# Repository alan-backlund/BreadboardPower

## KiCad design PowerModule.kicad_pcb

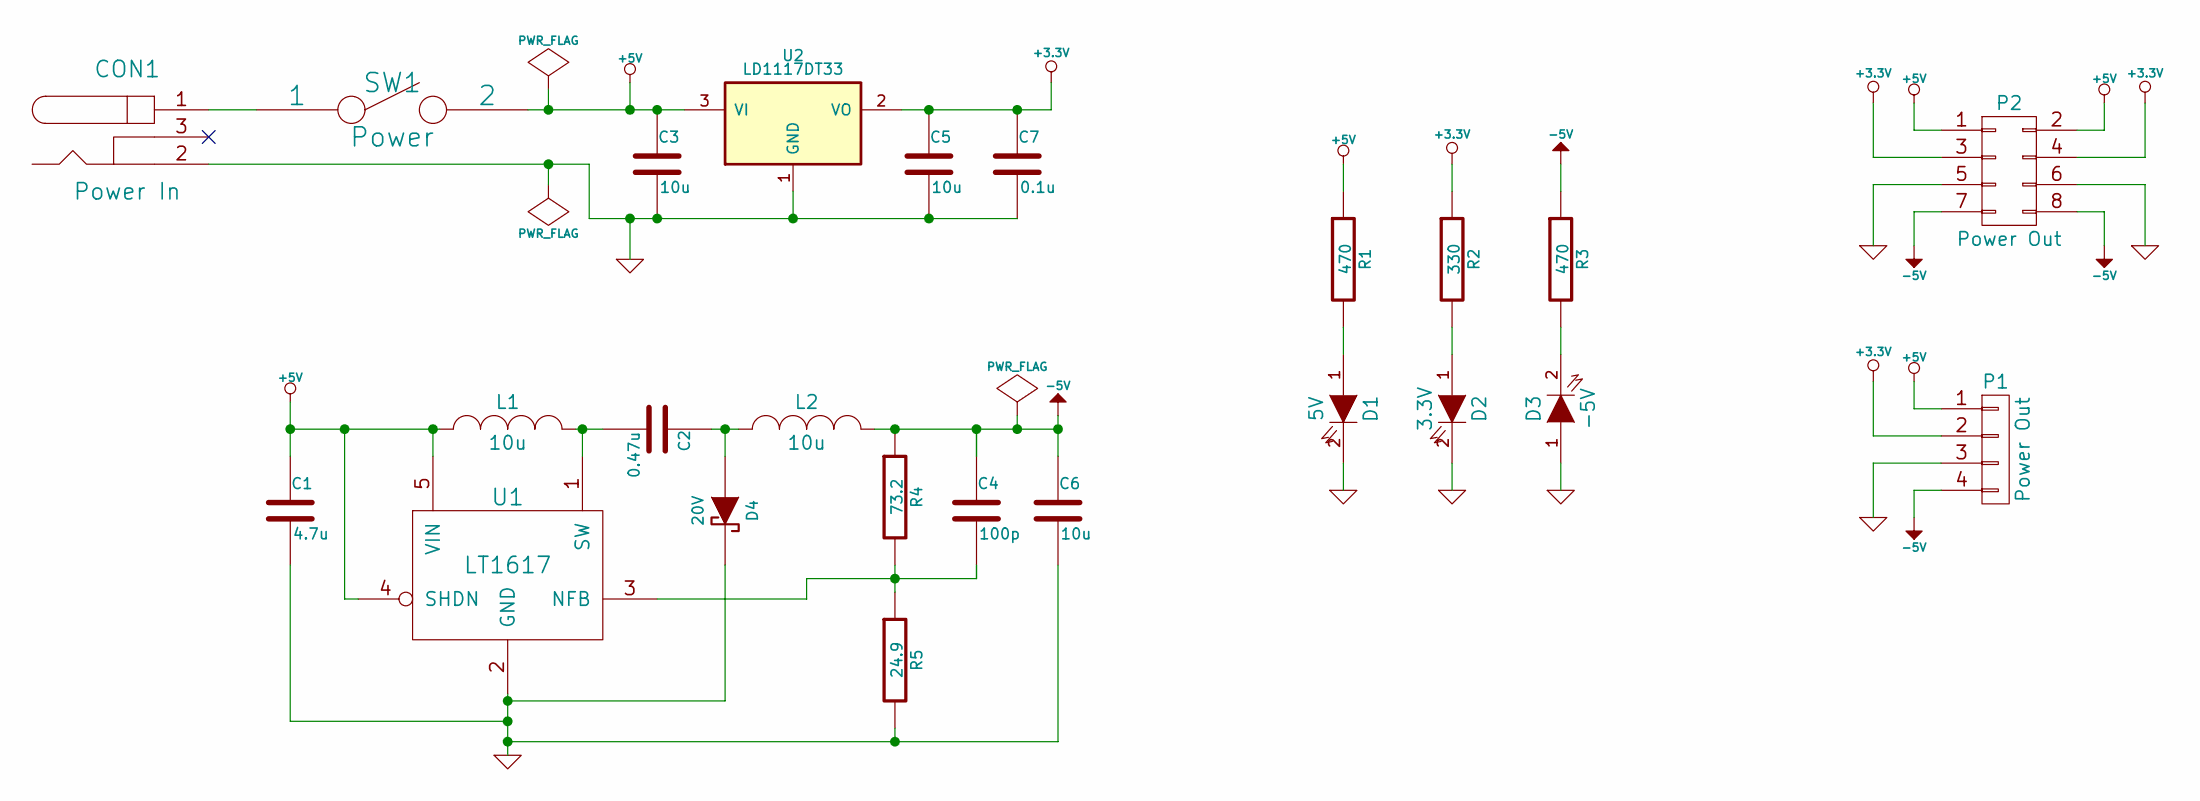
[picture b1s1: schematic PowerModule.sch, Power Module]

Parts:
C1: 4.7u; C_1206_HandSoldering
C2: 0.47u; C_0805_HandSoldering
C3, C5: 10u; C_0805_HandSoldering
C4: 100p; C_0805_HandSoldering
C6: 10u; C_1206_HandSoldering
C7: 0.1u; C_0805_HandSoldering
CON1: Power In; DC_PWR_JACK
D1: 5V; C_0805_HandSoldering
D2: 3.3V; C_0805_HandSoldering
D3: -5V; C_0805_HandSoldering
D4: 20V; SOD-123
L1, L2: 10u; C_0805_HandSoldering
P1: Power Out; 4pinTerminal
P2: Power Out; Pin_Header_Straight_2x04
R1, R3: 470; R_0805_HandSoldering
R2: 330; R_0805_HandSoldering
R4: 73.2; R_0805_HandSoldering
R5: 24.9; R_0805_HandSoldering
SW1: Power; PVA2EE
U1: LT1617; SOT-23-5
U2: LD1117DT33; DPAK

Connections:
+3.3V: C5.1, C7.1, P1.2, P2.3, P2.4, R2.1, U2.2 (VO)
+5V: C1.1, C3.1, L1.1, P1.1, P2.1, P2.2, R1.1, SW1.2, U1.4 (SHDN), U1.5 (VIN), U2.3 (VI)
-5V: C4.1, C6.1, L2.2, P1.4, P2.7, P2.8, R3.1, R4.1
GND: C1.2, C3.2, C5.2, C6.2, C7.2, CON1.2, D1.2 (K), D2.2 (K), D3.1 (A), D4.2 (K), P1.3, P2.5, P2.6, R5.2, U1.2 (GND), U2.1 (GND)
unnamed: C2.1, D4.1 (A), L2.1
unnamed: C2.2, L1.2, U1.1 (SW)
unnamed: C4.2, R4.2, R5.1, U1.3 (NFB)
unnamed: CON1.1, SW1.1
unnamed: D1.1 (A), R1.2
unnamed: D2.1 (A), R2.2
unnamed: D3.2 (K), R3.2

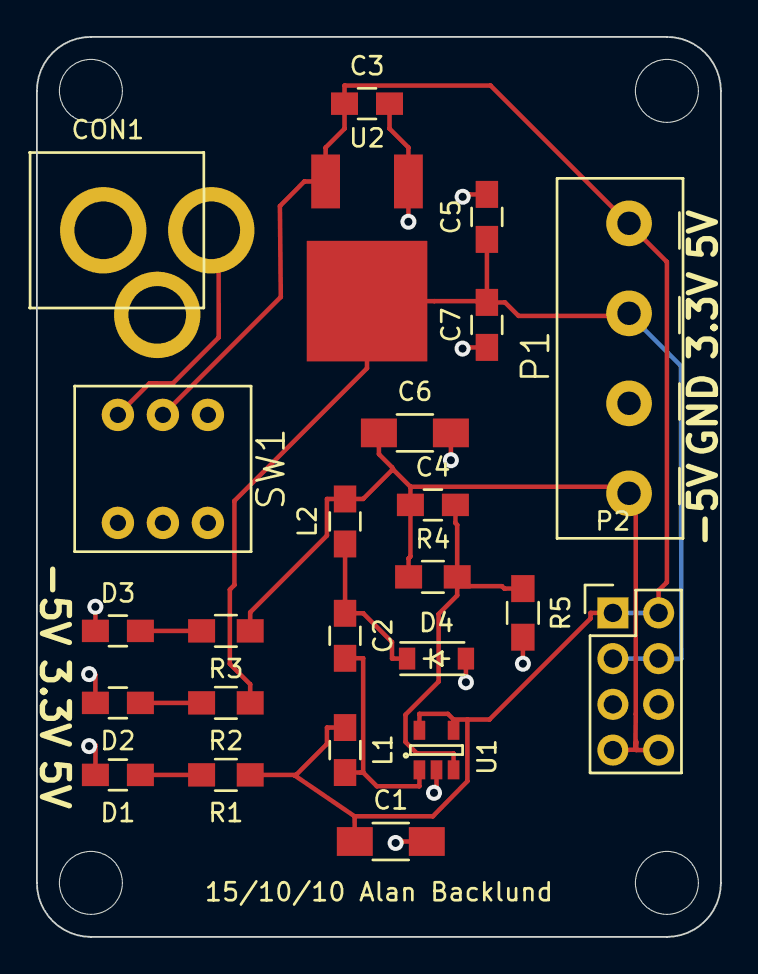
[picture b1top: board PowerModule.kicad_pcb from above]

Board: 2 copper layers, 38.0 x 50.0 mm, 28 parts (0 on the bottom side), 11 nets.

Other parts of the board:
REF1, REF2, REF3, REF4: MountingHole_3-5mm

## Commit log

2015-10-10 Schematic done, parts layed out but not traces.
2015-10-10 Tracks laid out.
2015-10-11 Clean
2015-10-30 OSH Park build works
2016-01-27 Clean for posting.
2016-01-27 Clean for posting 2.
